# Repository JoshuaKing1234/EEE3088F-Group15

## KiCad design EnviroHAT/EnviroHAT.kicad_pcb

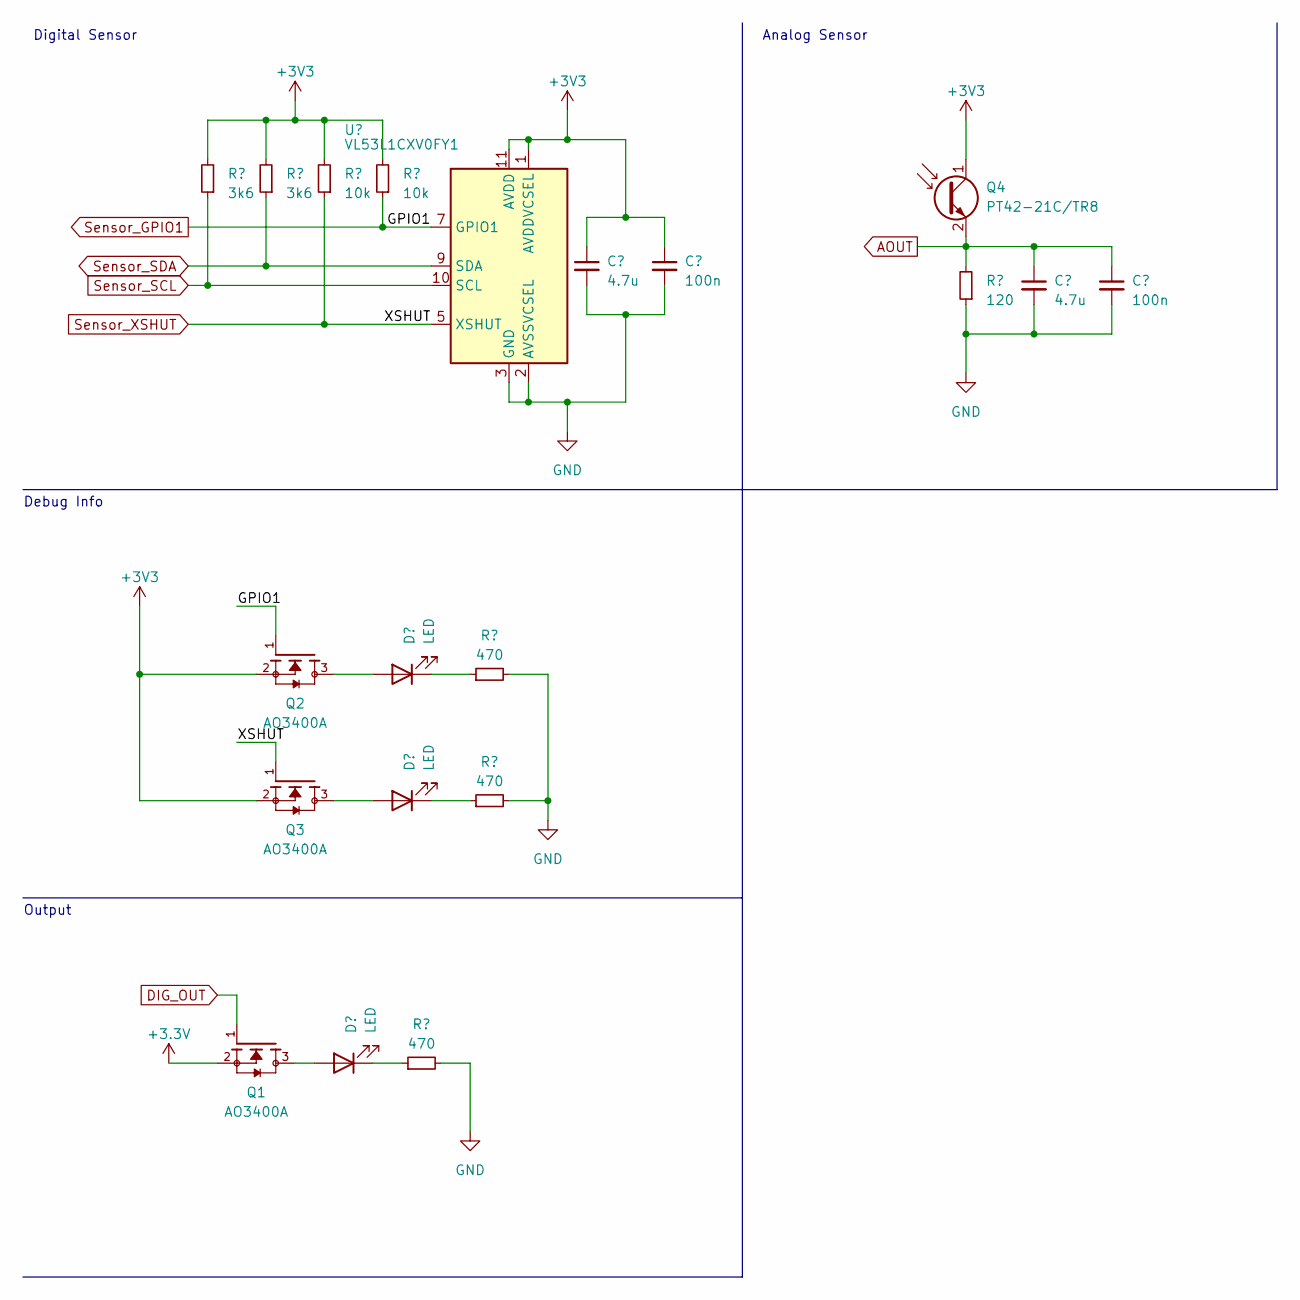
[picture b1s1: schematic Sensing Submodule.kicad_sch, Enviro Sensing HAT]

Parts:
C11, C13: 4.7u; C_1206_3216Metric
C12, C14: 100n; C_1206_3216Metric
D3, D4, D5: LED; LED_0805_2012Metric
Q1, Q2, Q3: AO3400A; SOT95P280X125-3N; PARTREV L
Q4: PT42-21C/TR8; LED_1210_3225Metric
R5, R6: 3k6; R_1206_3216Metric
R7, R8: 10k; R_1206_3216Metric
R9, R10, R11: 470; R_1206_3216Metric
R12: 120; R_1206_3216Metric
U4: VL53L1CXV0FY1; ST_VL53L1x

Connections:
+3.3V: Q1.2; also elsewhere on the board
+3V3: C11.1, C12.1, Q2.2, Q3.2, Q4.1 (C), R5.2, R6.2, R7.2, R8.2, U4.1 (AVDDVCSEL), U4.11 (AVDD); also elsewhere on the board
AOUT: C13.1, C14.1, Q4.2 (E), R12.2; also elsewhere on the board
DIG_OUT: Q1.1; also elsewhere on the board
GND: C11.2, C12.2, C13.2, C14.2, R9.2, R10.2, R11.2, R12.1, U4.2 (AVSSVCSEL), U4.3 (GND), U4.4 (GND), U4.6 (GND), U4.12 (GND); also elsewhere on the board
unnamed: D3.2 (A), Q1.3
unnamed: D3.1 (K), R9.1
unnamed: D4.2 (A), Q2.3
unnamed: D4.1 (K), R10.1
unnamed: D5.2 (A), Q3.3
unnamed: D5.1 (K), R11.1
Sensor_GPIO1: Q2.1, R8.1, U4.7 (GPIO1); also elsewhere on the board
Sensor_SCL: R5.1, U4.10 (SCL); also elsewhere on the board
Sensor_SDA: R6.1, U4.9 (SDA); also elsewhere on the board
Sensor_XSHUT: Q3.1, R7.1, U4.5 (XSHUT); also elsewhere on the board

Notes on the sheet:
Debug Info
Output
Digital Sensor
Analog Sensor

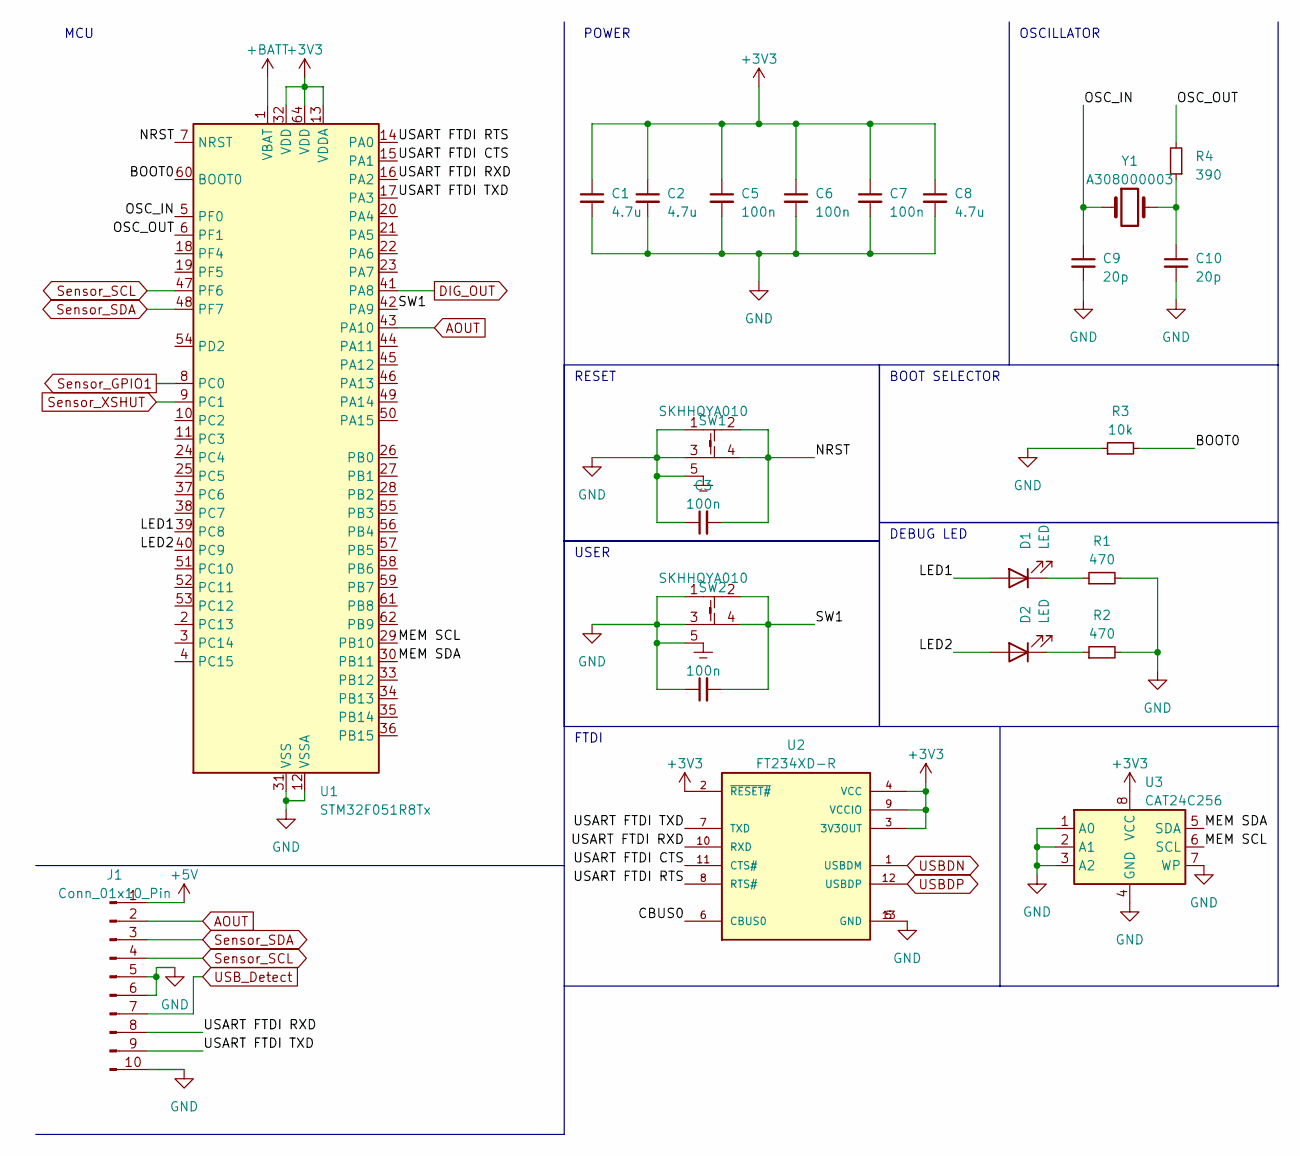
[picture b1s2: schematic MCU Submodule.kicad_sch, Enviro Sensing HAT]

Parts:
C1, C2, C8: 4.7u; C_1206_3216Metric
C3, C4, C5, C6, C7: 100n; C_1206_3216Metric
C9, C10: 20p; C_1206_3216Metric
D1, D2: LED; LED_0805_2012Metric
J1: Conn_01x10_Pin; PinHeader_1x10_P1.00mm_Vertical
R1, R2: 470; R_1206_3216Metric
R3: 10k; R_1206_3216Metric
R4: 390; R_1206_3216Metric
SW1, SW2: SKHHQYA010
U1: STM32F051R8Tx; LQFP-64_10x10mm_P0.5mm
U2: FT234XD-R; SON45P300X300X80-13N; PARTREV Version 1.2
U3: CAT24C256; SOIC127P600X175-8N
Y1: A308000003; Crystal_SMD_3225-2Pin_3.2x2.5mm

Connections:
+3V3: C1.1, C2.1, C5.1, C6.1, C7.1, C8.1, U1.13 (VDDA), U1.32 (VDD), U1.64 (VDD), U2.2 (~RESET#), U2.3 (3V3OUT), U2.4 (VCC), U2.9 (VCCIO), U3.8 (VCC); also elsewhere on the board
+BATT: U1.1 (VBAT); also elsewhere on the board
/MCU Submodule/BOOT0: R3.2, U1.60 (BOOT0)
/MCU Submodule/CBUS0: U2.6 (CBUS0)
/MCU Submodule/LED1: D1.2 (A), U1.39 (PC8)
/MCU Submodule/LED2: D2.2 (A), U1.40 (PC9)
/MCU Submodule/MEM SCL: U1.29 (PB10), U3.6 (SCL)
/MCU Submodule/MEM SDA: U1.30 (PB11), U3.5 (SDA)
/MCU Submodule/NRST: C3.2, SW1.2, SW1.4, U1.7 (NRST)
/MCU Submodule/OSC_IN: C9.1, U1.5 (PF0), Y1.1
/MCU Submodule/OSC_OUT: R4.2, U1.6 (PF1)
/MCU Submodule/SW1: C4.2, SW2.2, SW2.4, U1.42 (PA9)
/MCU Submodule/USART FTDI CTS: U1.15 (PA1), U2.11 (CTS#)
/MCU Submodule/USART FTDI RTS: U1.14 (PA0), U2.8 (RTS#)
/MCU Submodule/USART FTDI RXD: J1.8, U1.16 (PA2), U2.10 (RXD)
/MCU Submodule/USART FTDI TXD: J1.9, U1.17 (PA3), U2.7 (TXD)
AOUT: J1.2, U1.43 (PA10); also elsewhere on the board
DIG_OUT: U1.41 (PA8); also elsewhere on the board
GND: C1.2, C2.2, C3.1, C4.1, C5.2, C6.2, C7.2, C8.2, C9.2, C10.2, J1.5, J1.6, J1.10, R1.2, R2.2, R3.1, SW1.1, SW1.3, SW1.5, SW2.1, SW2.3, SW2.5, U1.12 (VSSA), U1.31 (VSS), U1.63 (VSS), U2.5 (GND), U2.13 (GND), U3.1 (A0), U3.2 (A1), U3.3 (A2), U3.4 (GND), U3.7 (WP); also elsewhere on the board
unnamed: C10.1, R4.1, Y1.2
unnamed: D1.1 (K), R1.1
unnamed: D2.1 (K), R2.1
Sensor_GPIO1: U1.8 (PC0); also elsewhere on the board
Sensor_SCL: J1.4, U1.47 (PF6); also elsewhere on the board
Sensor_SDA: J1.3, U1.48 (PF7); also elsewhere on the board
Sensor_XSHUT: U1.9 (PC1); also elsewhere on the board
USBDN: U2.1 (USBDM); also elsewhere on the board
USBDP: U2.12 (USBDP); also elsewhere on the board
USB_Detect: J1.1, J1.7; also elsewhere on the board

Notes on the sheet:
BOOT SELECTOR
RESET
POWER
USER
MCU
OSCILLATOR
FTDI
DEBUG LED

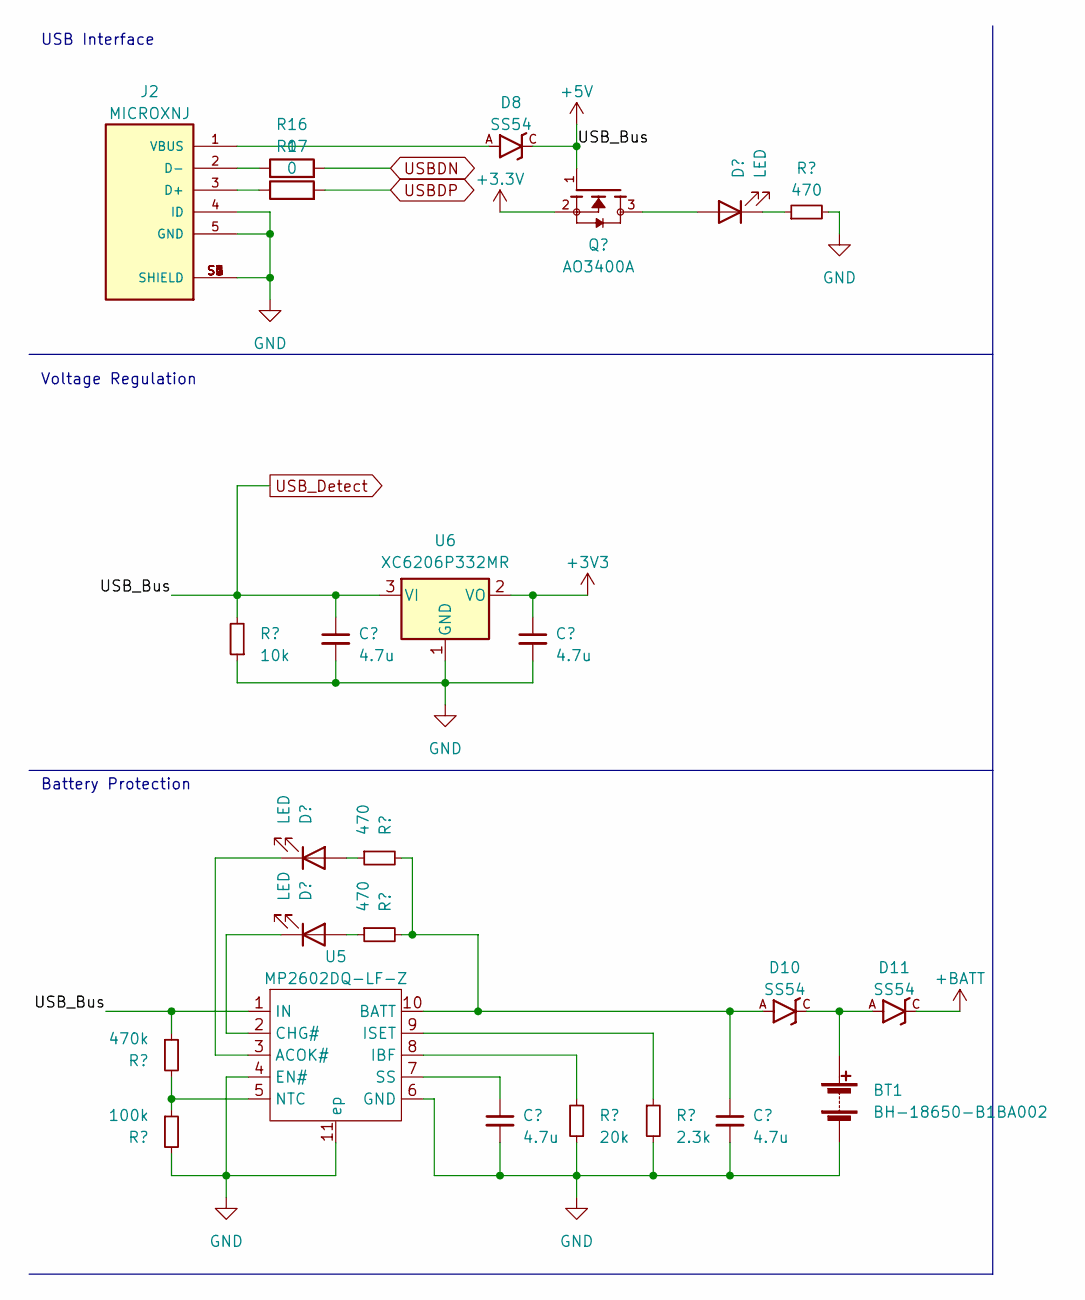
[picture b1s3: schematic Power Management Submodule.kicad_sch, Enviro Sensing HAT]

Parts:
BT1: BH-18650-B1BA002
C15, C16, C17, C18: 4.7u; C_1206_3216Metric
D6, D7, D9: LED; LED_0805_2012Metric
D8, D10, D11: SS54; DO-214AC
J2: MICROXNJ; SHOUHAN_MICROXNJ; PARTREV A
Q5: AO3400A; SOT95P280X125-3N; PARTREV L
R13: 470k; R_1206_3216Metric
R14: 100k; R_1206_3216Metric
R15: 10k; R_1206_3216Metric
R16, R17: 0; R_1206_3216Metric_Pad1.30x1.75mm_HandSolder
R18, R19, R22: 470; R_1206_3216Metric
R20: 20k; R_1206_3216Metric
R21: 2.3k; R_1206_3216Metric
U5: MP2602DQ-LF-Z; SON50P300X300X100-11N
U6: XC6206P332MR; SOT-23-3

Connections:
+3.3V: Q5.2; also elsewhere on the board
+3V3: C16.1, U6.2 (VO); also elsewhere on the board
+BATT: D11.C; also elsewhere on the board
GND: BT1.2 (-), C15.2, C16.2, C17.2, C18.2, J2.4 (ID), J2.5 (GND), J2.S1 (SHIELD), J2.S2 (SHIELD), J2.S3 (SHIELD), J2.S4 (SHIELD), J2.S5 (SHIELD), J2.S6 (SHIELD), R14.2, R15.1, R20.1, R21.2, R22.2, U5.4 (EN#), U5.6 (GND), U5.11 (ep), U6.1 (GND); also elsewhere on the board
unnamed: BT1.1 (+), D10.C, D11.A
unnamed: D6.2 (A), R18.1
unnamed: D6.1 (K), U5.3 (ACOK#)
unnamed: D7.2 (A), R19.1
unnamed: D7.1 (K), U5.2 (CHG#)
unnamed: D9.2 (A), Q5.3
unnamed: D9.1 (K), R22.1
unnamed: J2.3 (D+), R17.1
unnamed: J2.2 (D-), R16.1
unnamed: D8.A, J2.1 (VBUS)
unnamed: C18.1, D10.A, R18.2, R19.2, U5.10 (BATT)
unnamed: R20.2, U5.8 (IBF)
unnamed: R21.1, U5.9 (ISET)
unnamed: R13.2, R14.1, U5.5 (NTC)
unnamed: C17.1, U5.7 (SS)
USBDN: R16.2; also elsewhere on the board
USBDP: R17.2; also elsewhere on the board
USB_Detect: C15.1, D8.C, Q5.1, R13.1, R15.2, U5.1 (IN), U6.3 (VI); also elsewhere on the board

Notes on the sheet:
Battery Protection
Voltage Regulation
USB Interface

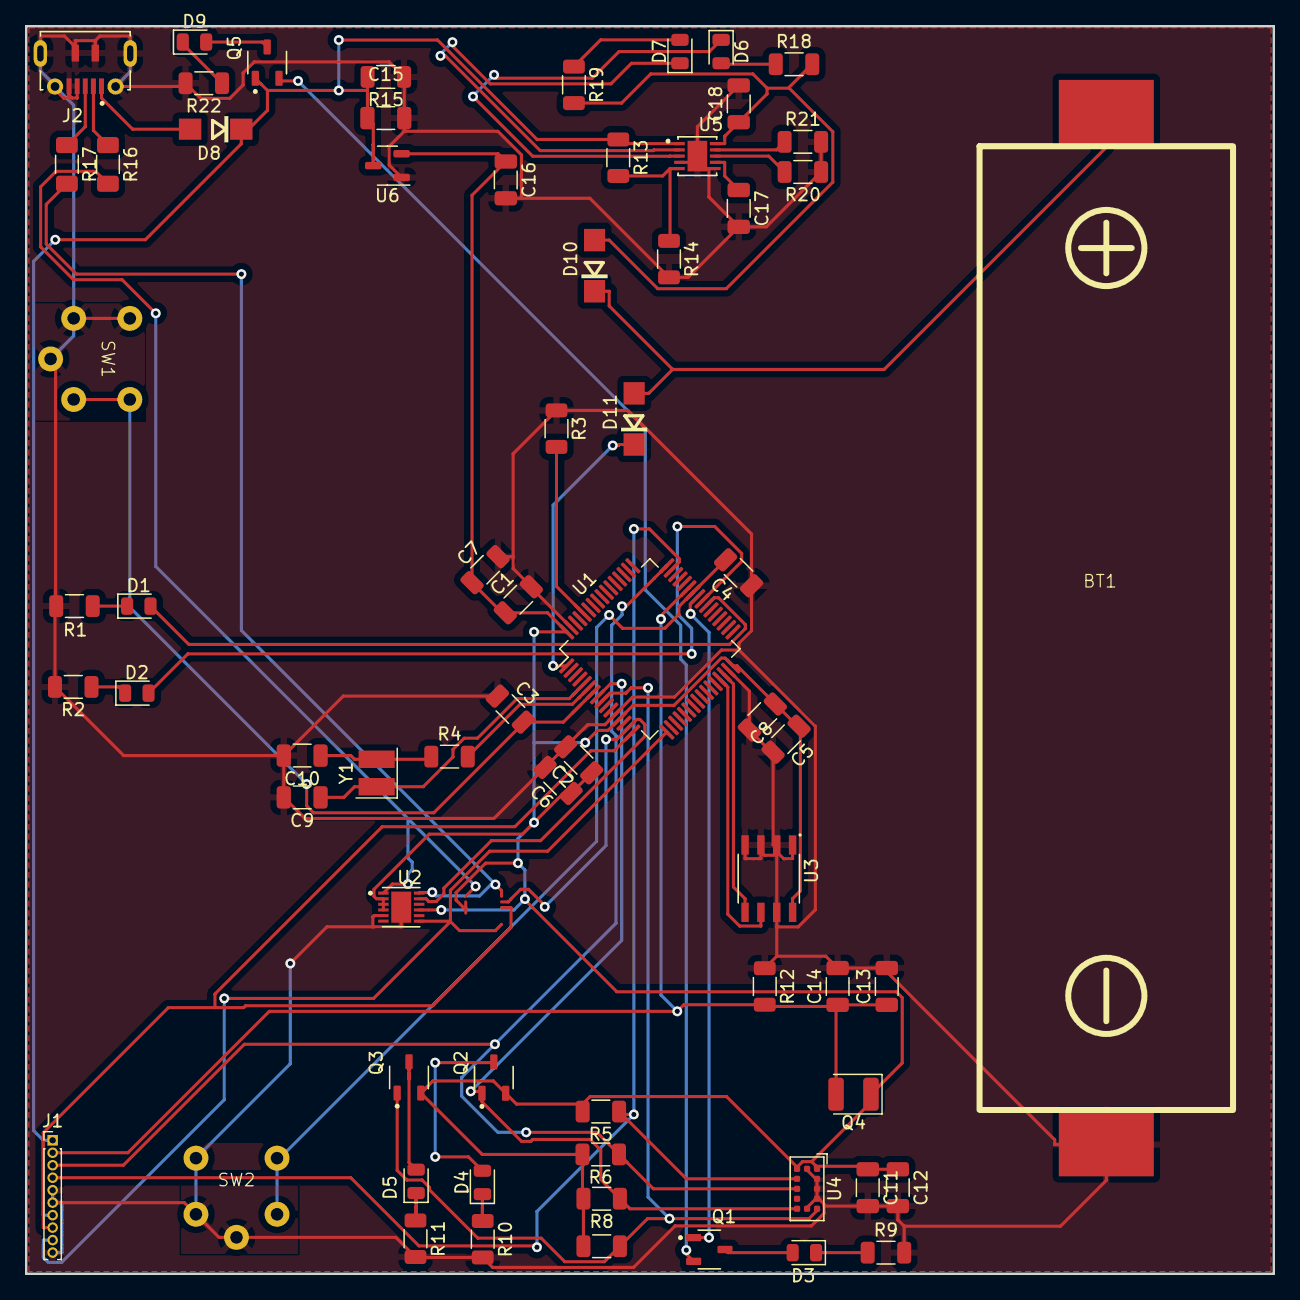
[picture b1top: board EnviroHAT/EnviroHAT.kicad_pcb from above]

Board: 2 copper layers, 100.0 x 100.0 mm, 68 parts (0 on the bottom side), 50 nets.

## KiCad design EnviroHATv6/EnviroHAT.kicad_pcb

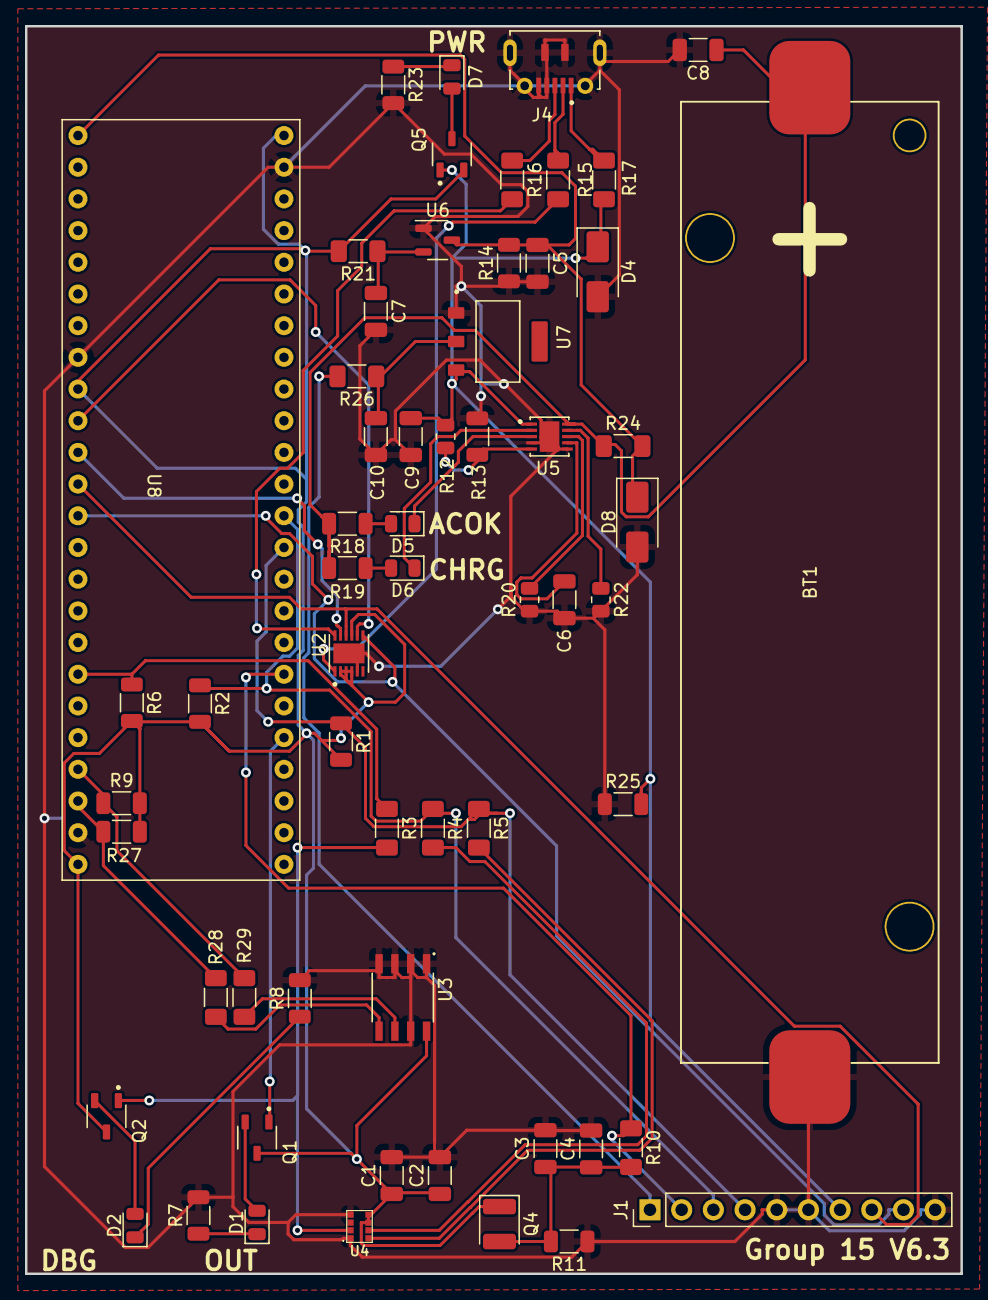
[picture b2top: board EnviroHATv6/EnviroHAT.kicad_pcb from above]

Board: 2 copper layers, 75.0 x 100.0 mm, 60 parts (0 on the bottom side), 44 nets.

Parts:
BT1: BH-18650-B1BA002; 18650_Holder_SMD
C1, C3, C5, C6, C7, C8, C9, C10: 4.7u; C_1206_3216Metric
C2, C4: 100n; C_1206_3216Metric
D1, D2, D5, D6, D7: LED; LED_0805_2012Metric
D4, D8: M7; D_SMA
J1: Conn_01x10_Pin; PinHeader_1x10_P2.54mm_Vertical
J4: MICROXNJ; SHOUHAN_MICROXNJ
Q1, Q2, Q5: AO3400A; SOT95P280X125-3N
Q4: PT42-21C/TR8; LED_1210_3225Metric
R1, R2, R9, R27: 3k6; R_1206_3216Metric
R3, R4, R5, R10, R15, R16, R17, R21, R24, R26, R28, R29: 0; R_1206_3216Metric_Pad1.30x1.75mm_HandSolder
R6, R14, R25: 10k; R_1206_3216Metric
R7, R8, R18, R19, R23: 470; R_1206_3216Metric
R11: 1k; R_1206_3216Metric
R12: 470k; R_0805_2012Metric
R13: 100k; R_1206_3216Metric
R20: 20k; R_0805_2012Metric
R22: 2.2k; R_0805_2012Metric
U2: FT234XD-R; SON45P300X300X80-13N
U3: CAT24C256; SOIC127P600X175-8N
U4: VCNL36821S
U5: MP2602DQ-LF-Z; SON50P300X300X100-11N
U6: XC6206P332MR; SOT-23-3
U7: AMS1117-5.0; SOT229P700X180-4N
U8: STM32F051C6T6

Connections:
+3V3: C1.1, C2.1, Q1.3, Q2.3, Q4.1 (C), Q5.2, R1.2, R2.2, R6.2, R9.2, R21.2, R27.2, U2.2 (~RESET#), U2.3 (3V3OUT), U2.4 (VCC), U2.9 (VCCIO), U3.8 (VCC), U4.P$5 (LED), U4.P$6 (VDD), U8.9 (V+), U8.24 (V+), U8.48 (V+)
+5V: J1.1, R26.2
+BATT: C5.1, D8.1 (K), R14.2, R24.2, U6.3 (VI), U8.1 (VBAT)
/MCU Submodule/MEM SCL: R9.1, R29.2, U8.21 (PB10)
/MCU Submodule/MEM SDA: R27.1, R28.2, U8.22 (PB11)
/MCU Submodule/USART FTDI CTS: U2.11 (CTS#), U8.11 (PA1)
/MCU Submodule/USART FTDI RTS: U2.8 (RTS#), U8.10 (PA0)
/MCU Submodule/USART FTDI RXD: J1.8, U2.10 (RXD), U8.12 (PA2)
/MCU Submodule/USART FTDI TXD: J1.9, U2.7 (TXD), U8.13 (PA3)
/Sensing Submodule/GPIO1: Q2.1, R3.2, U4.P$2 (INT)
AOUT: J1.2, R10.1, U8.31 (PA10)
DIG_OUT: Q1.1, U8.29 (PA8)
GND: BT1.2 (-), C1.2, C2.2, C3.2, C4.2, C5.2, C6.2, C7.2, C8.2, C9.2, C10.2, D4.2 (A), D8.2 (A), J1.5, J1.6, J1.10, J4.4 (ID), J4.5 (GND), J4.S1 (SHIELD), J4.S2 (SHIELD), J4.S3 (SHIELD), J4.S4 (SHIELD), J4.S5 (SHIELD), J4.S6 (SHIELD), R7.2, R8.2, R11.1, R13.2, R14.1, R20.1, R22.2, R23.2, R25.1, U2.5 (GND), U2.13 (GND), U3.1 (A0), U3.2 (A1), U3.3 (A2), U3.4 (GND), U3.7 (WP), U4.P$1 (GND), U4.P$4 (GND1), U5.4 (EN#), U5.6 (GND), U5.11 (ep), U6.1 (GND), U7.1 (GND/ADJ), U8.8 (GND), U8.23 (GND), U8.47 (GND)
unnamed: BT1.1 (+), C8.1, R18.2, R19.2, R24.1, U5.10 (BATT)
unnamed: D1.2 (A), Q1.2
unnamed: D1.1 (K), R7.1
unnamed: D2.2 (A), Q2.2
unnamed: D2.1 (K), R8.1
unnamed: D5.2 (A), R18.1
unnamed: D5.1 (K), U5.3 (ACOK#)
unnamed: D6.2 (A), R19.1
unnamed: D6.1 (K), U5.2 (CHG#)
unnamed: D7.2 (A), Q5.3
unnamed: D7.1 (K), R23.1
unnamed: J4.3 (D+), R16.1
unnamed: J4.2 (D-), R15.1
unnamed: J4.1 (VBUS), R17.1
unnamed: C3.1, C4.1, Q4.2 (E), R10.2, R11.2
unnamed: R29.1, U3.6 (SCL)
unnamed: R28.1, U3.5 (SDA)
unnamed: R5.2, U4.P$8 (SCL)
unnamed: R4.2, U4.P$7 (SDA)
unnamed: R20.2, U5.8 (IBF)
unnamed: R22.1, U5.9 (ISET)
unnamed: R12.2, R13.1, U5.5 (NTC)
unnamed: C6.1, U5.7 (SS)
unnamed: C7.1, R21.1, U6.2 (VO)
unnamed: C10.1, R26.1, U7.2 (VOUT)
Sensor_GPIO1: R3.1, R6.1, U8.18 (PB0)
Sensor_SCL: J1.4, R1.1, R5.1, U8.35 (PF6)
Sensor_SDA: J1.3, R2.1, R4.1, U8.36 (PF7)
USBDN: R15.2, U2.1 (USBDM)
USBDP: R16.2, U2.12 (USBDP)
USB_Detect: C9.1, D4.1 (K), J1.7, Q5.1, R12.1, R17.2, R25.2, U5.1 (IN), U7.3 (VIN)

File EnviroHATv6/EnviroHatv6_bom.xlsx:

Comment | Designator | Footprint | JLCPCB Part #（optional）
2.2k | R22 | R_0805_2012Metric | C17520
20k | R20 | R_0805_2012Metric | C4328
470k | R12 | R_0805_2012Metric | C17709
LED | D5,D1,D2,D7,D6 | LED_0805_2012Metric | C2297
0 | R4,R17,R15,R10,R21,R5,R3,R16,R24,R26,R28,R29 | R_1206_3216Metric_Pad1.30x1.75mm_HandSolder | C17888
AO3400A | Q2,Q5,Q1 | SOT95P280X125-3N | C20917
470 | R7,R19,R18,R8,R23 | R_1206_3216Metric | C17936
4.7u | C3,C10,C5,C7,C9,C1,C6,C8 | C_1206_3216Metric | C96123
AMS1117-5.0 | U7 | SOT229P700X180-4N | C6187
PT42-21C/TR8 | Q4 | LED_1210_3225Metric | C264569
3k6 | R2,R1,R9,R27 | R_1206_3216Metric | C176265
1k | R11 | R_1206_3216Metric | C4410
XC6206P332MR | U6 | SOT-23-3 | C5446
10k | R6,R14,R25 | R_1206_3216Metric | C17928
M7 | D8,D4 | D_SMA | C95872
VCNL36821S | U4 | VCNL36821S | C1850419
FT234XD-R | U2 | SON45P300X300X80-13N | C132158
MP2602DQ-LF-Z | U5 | SON50P300X300X100-11N | C44515
100n | C2,C4 | C_1206_3216Metric | C24497
MICROXNJ | J4 | SHOUHAN_MICROXNJ | C404969
100k | R13 | R_1206_3216Metric | C17900
CAT24C256 | U3 | SOIC127P600X175-8N | C79987

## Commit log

2023-03-06 Create BOM sensors
2023-03-13 Update BOM sensors
2023-04-24 PCB Cleanup V6.3
2023-05-08 Submission 3
